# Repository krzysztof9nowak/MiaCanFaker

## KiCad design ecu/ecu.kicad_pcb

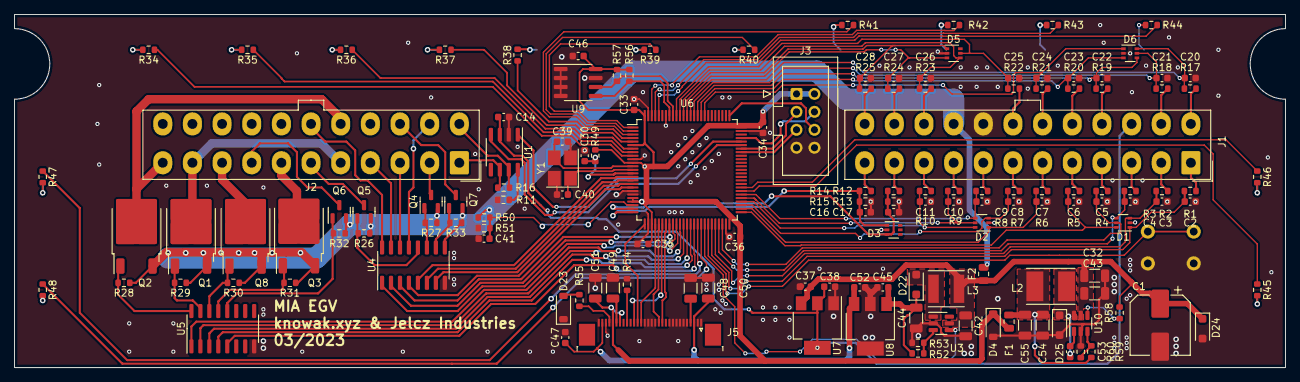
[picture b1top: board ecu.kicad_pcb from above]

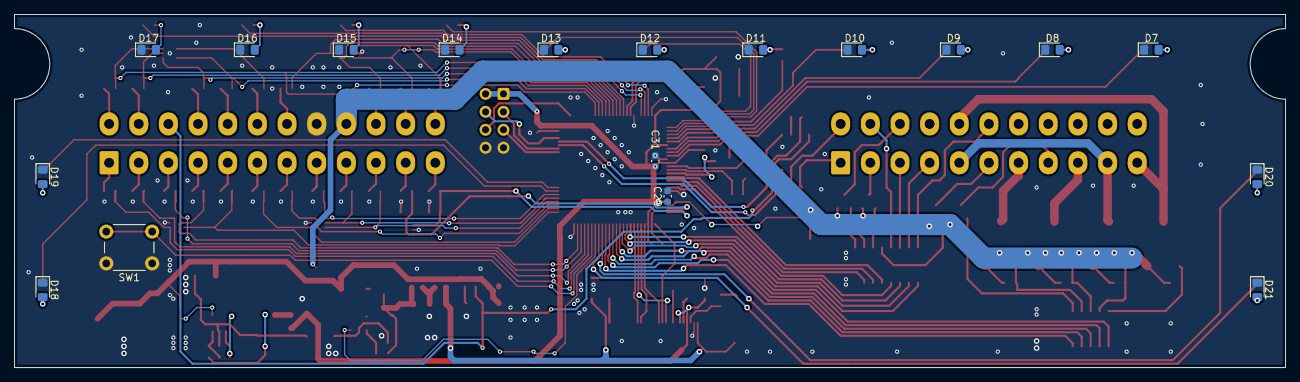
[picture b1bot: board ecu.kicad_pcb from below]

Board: 2 copper layers, 180.0 x 50.0 mm, 162 parts (18 on the bottom side), 145 nets.

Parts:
C1: 100uF 25V; CP_Elec_8x6.2
C2, C3, C4, C5, C6, C7, C8, C9, C10, C11, C14, C16, C17, C20, C21, C22, C23, C24, C25, C26, C27, C28, C41, C46: 100nF; C_0603_1608Metric
C29, C31, C33, C34, C35, C37, C38: 1uF; C_0603_1608Metric
C30, C53: 100n; C_0603_1608Metric
C32, C42, C43, C44, C48, C49, C50, C51: 10uF 25V; C_1206_3216Metric
C36: 4.7u; C_0603_1608Metric
C39, C40: 18pF; C_0603_1608Metric
C45, C47, C52: 0.1uF; C_0603_1608Metric
C54, C55: 22uF 10V; C_1206_3216Metric
D1, D2, D3, D5, D6: PESD3V3L5UY; SOT-363_SC-70-6
D4: BZT52C3V6; D_SOD-123
D7, D8, D9, D10, D11, D12, D13, D14, D15, D16, D17, D18, D19, D20, D21: RED; LED_0805_2012Metric_Pad1.15x1.40mm_HandSolder
D22, D24: SK12WA; D_SOD-123F
D23: 1N4148; D_SOD-123
D25: SK14WA; D_SOD-123F
F1, F2: 250mA; Fuse_0805_2012Metric
J1: INPUTS; Molex_Mini-Fit_Jr_5566-24A_2x12_P4.20mm_Vertical
J2: OUTPUTS; Molex_Mini-Fit_Jr_5566-22A_2x11_P4.20mm_Vertical
J3: DEBUG; IDC-Header_2x04_P2.54mm_Vertical
J5: OLED; TE_3-1734839-0_1x30-1MP_P0.5mm_Horizontal
L2: 22uH 900mA; L_Taiyo-Yuden_NR-50xx_HandSoldering
L3: 22uH; L_Taiyo-Yuden_NR-50xx
Q1, Q2, Q3, Q8: AOD4185; TO-252-2
Q4, Q5, Q6, Q7: BXT3800P06M; SOT-23
R1, R2, R3, R4, R5, R6, R7, R8, R9, R10, R12, R13, R14, R15, R17, R18, R19, R20, R21, R22, R23, R24, R25, R26, R27, R28, R29, R30, R31, R32, R33, R49, R51, R56, R57, R58, R59: 10k; R_0603_1608Metric
R11, R53: 1k; R_0603_1608Metric
R16: DNP; R_0603_1608Metric
R34, R35, R36, R37, R38, R39, R40, R41, R42, R43, R44, R45, R46, R47, R48: 220; R_0603_1608Metric
R50: 100k; R_0603_1608Metric
R52: 29k; R_0603_1608Metric
R54: 910k; R_0603_1608Metric
R55: 50; R_0603_1608Metric
R60: 3k; R_0603_1608Metric
SW1: DISP_BUTTON; SW_PUSH_6mm_H13mm
U1: MCP2551-I-SN; SOIC-8_3.9x4.9mm_P1.27mm
U3: SB6286; SOT-23-6
U4, U5: ULN2003; SOP-16_3.9x9.9mm_P1.27mm
U6: STM32F103VETx; LQFP-100_14x14mm_P0.5mm
U7: AMS1117-5.0; SOT-223-3_TabPin2
U8: 78L15MG-AA3-R; SOT-223-3_TabPin2
U9: FM24CL16B; SOIC-8_3.9x4.9mm_P1.27mm
U10: AOZ1282CI-1; SOT-23-6
Y1: 16MHz; Crystal_SMD_3225-4Pin_3.2x2.5mm_HandSoldering

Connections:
+3V3: C29.1, C31.1, C33.1, C34.1, C35.1, C36.1, C46.1, C51.1, D4.1 (K), F1.2, J3.1, J3.2, J5.24, J5.26, R49.1, R56.1, R57.1, U6.6 (VBAT), U6.11 (VDD), U6.21 (VREF+), U6.22 (VDDA), U6.28 (VDD), U6.50 (VDD), U6.75 (VDD), U6.100 (VDD), U9.8 (VDD)
+5V: C14.1, C38.1, J1.15, U1.3 (VDD), U7.2 (VO)
+12V: F2.2, J1.21, Q1.3 (S), Q2.3 (S), Q3.3 (S), Q4.2 (S), Q5.2 (S), Q6.2 (S), Q7.2 (S), Q8.3 (S), R26.1, R27.1, R28.1, R29.1, R30.1, R31.1, R32.1, R33.1, R50.1, U4.9 (COM)
+15V: C47.1, C50.1, C52.1, J5.3, J5.29, U8.3 (OUT)
/APC: U4.7 (I7), U6.17 (PC2)
/APC_H: J2.14, Q7.3 (D)
/BMS: U4.1 (I1), U6.35 (PB0)
/BMS_L: J2.17, U4.16 (O1)
/CAN1_RX: U1.4 (RXD), U6.70 (PA11)
/CAN1_TX: U1.1 (TXD), U6.71 (PA12)
/CAN_H: J2.12, R16.1, U1.7 (CANH)
/CAN_L: J2.1, R16.2, U1.6 (CANL)
/HEATING: U5.5 (I5), U6.40 (PE9)
/HEATING_H: J2.8, Q6.3 (D)
/INDIC_LEFT: U5.1 (I1), U6.36 (PB1)
/INDIC_LEFT_H: J2.11, J2.16, Q2.2 (D)
/INDIC_RIGHT: U5.2 (I2), U6.37 (PB2)
/INDIC_RIGHT_H: J2.5, J2.10, Q1.2 (D)
/INVERTER: U4.4 (I4), U6.18 (PC3)
/INVERTER_L: J2.13, U4.13 (O4)
/IN_AIRBAG: C20.1, D6.6 (K5), R17.1, U6.87 (PD6)
/IN_BRAKE_1: C10.1, D2.5 (K4), R9.1, U6.55 (PD8)
/IN_CEINT: C2.1, D1.1 (K1), R1.1, U6.45 (PE14)
/IN_CRASH: C28.1, D5.1 (K1), R25.1, U6.89 (PB3)
/IN_CTL_APC: C3.1, D1.3 (K2), R2.1, U6.46 (PE15)
/IN_DF_CONV: C22.1, D6.4 (K3), R19.1, U6.85 (PD4)
/IN_DISP: SW1.2 (B), U6.44 (PE13)
/IN_DRIVE_DIR_1: C6.1, D1.6 (K5), R5.1, U6.51 (PB12)
/IN_DRIVE_DIR_2: C23.1, D6.3 (K2), R20.1, U6.84 (PD3)
/IN_ECO: C4.1, D1.4 (K3), R3.1, U6.47 (PB10)
/IN_FOG_LIGHT: C8.1, D2.3 (K2), R7.1, U6.53 (PB14)
/IN_HIGHBEAM: C25.1, D5.5 (K4), R22.1, U6.91 (PB5)
/IN_INDICATOR_RIGHT: C9.1, D2.4 (K3), R8.1, U6.56 (PD9)
/IN_KEY1: C26.1, D5.4 (K3), R23.1, U6.90 (PB4)
/IN_KEY2: C27.1, D5.3 (K2), R24.1, U6.88 (PD7)
/IN_PARK: C21.1, D6.5 (K4), R18.1, U6.86 (PD5)
/IN_SIDELIGHTS: C11.1, D2.6 (K5), R10.1, U6.54 (PB15)
/IN_WINDSHIELD_HEAT: C5.1, D1.5 (K4), R4.1, U6.48 (PB11)
/IN_WINDSHIELD_JET: C24.1, D6.1 (K1), R21.1, U6.83 (PD2)
/IN_WIPER: C7.1, D2.1 (K1), R6.1, U6.52 (PB13)
/LED_ABS: R41.1, U6.3 (PE4)
/LED_AIRBAG: R40.1, U6.2 (PE3)
/LED_BATTERY: R42.1, U6.98 (PE1)
/LED_BATTERY_HV: R48.1, U6.42 (PE11)
/LED_BELT: R38.1, U6.4 (PE5)
/LED_BRAKE: R37.1, U6.5 (PE6)
/LED_CHARGING: R47.1, U6.41 (PE10)
/LED_ELECTR: R35.1, U6.8 (PC14)
/LED_FOG: R43.1, U6.97 (PE0)
/LED_HEADLIGHT: R46.1, U6.58 (PD11)
/LED_HEATER: R44.1, U6.96 (PB9)
/LED_INDICATOR: R39.1, U6.1 (PE2)
/LED_SIDELIGHTS: R45.1, U6.57 (PD10)
/LED_STOP: R36.1, U6.7 (PC13)
/LED_TEMP: R34.1, U6.9 (PC15)
/LIGHT_DAYTIME: U4.6 (I6), U6.16 (PC1)
/LIGHT_DAYTIME_H: J2.2, Q4.3 (D)
/LIGHT_HAZARD: U4.5 (I5), U6.15 (PC0)
/LIGHT_HAZARD_H: J2.6, Q5.3 (D)
/LIGHT_REVERSE: U5.4 (I4), U6.39 (PE8)
/LIGHT_REVERSE_H: J2.7, Q3.2 (D)
/LIGHT_STOP: U5.3 (I3), U6.38 (PE7)
/LIGHT_STOP_H: J2.9, Q8.2 (D)
/OLED_CS: J5.19, U6.26 (PA3)
/OLED_DC: J5.18, U6.29 (PA4)
/OLED_MOSI: J5.12, U6.32 (PA7)
/OLED_POWER_EN: U3.4 (EN), U6.43 (PE12)
/OLED_RES: J5.20, U6.31 (PA6)
/OLED_SCK: J5.13, U6.30 (PA5)
/SCL: R57.2, U6.92 (PB6), U9.6 (SCL)
/SDA: R56.2, U6.93 (PB7), U9.5 (SDA)
/SWDCLK: J3.6, U6.76 (PA14)
/SWDIO: J3.4, U6.72 (PA13)
/THR1: C17.2, D3.3 (K2), R12.1, R13.2, U6.24 (PA1)
/THR2: C16.2, D3.1 (K1), R14.1, R15.2, U6.25 (PA2)
/USART1_RX: J3.3, U6.69 (PA10)
/USART1_TX: J3.5, U6.68 (PA9)
/VBAT_MEAS: C41.1, R50.2, R51.1, U6.23 (PA0)
/WINDSHIELD_HEAT: U4.3 (I3), U6.33 (PC4)
/WINDSHIELD_HEAT_L: J2.3, U4.14 (O3)
/WIPERS: U4.2 (I2), U6.34 (PC5)
/WIPERS_L: J2.4, U4.15 (O2)
GND: C1.2, C2.2, C3.2, C4.2, C5.2, C6.2, C7.2, C8.2, C9.2, C10.2, C11.2, C14.2, C16.1, C17.1, C20.2, C21.2, C22.2, C23.2, C24.2, C25.2, C26.2, C27.2, C28.2, C29.2, C30.2, C31.2, C32.2, C33.2, C34.2, C35.2, C36.2, C37.2, C38.2, C39.2, C40.2, C41.2, C42.2, C43.2, C44.2, C45.2, C46.2, C47.2, C48.2, C49.2, C50.2, C51.2, C52.2, C54.2, C55.2, D1.2 (A), D2.2 (A), D3.2 (A), D4.2 (A), D5.2 (A), D6.2 (A), D7.1 (K), D8.1 (K), D9.1 (K), D10.1 (K), D11.1 (K), D12.1 (K), D13.1 (K), D14.1 (K), D15.1 (K), D16.1 (K), D17.1 (K), D18.1 (K), D19.1 (K), D20.1 (K), D21.1 (K), D23.1 (K), D24.2 (A), D25.2 (A), J1.20, J3.7, J3.8, J5.1, J5.2, J5.5, J5.6, J5.7, J5.8, J5.9, J5.10, J5.14, J5.15, J5.16, J5.17, J5.28, J5.30, R11.2, R13.1, R15.1, R51.2, R53.1, R54.1, R60.1, SW1.1 (A), U1.2 (VSS), U3.2 (GND), U4.8 (GND), U5.8 (GND), U6.10 (VSS), U6.19 (VSSA), U6.20 (VREF-), U6.27 (VSS), U6.49 (VSS), U6.74 (VSS), U6.94 (BOOT0), U6.99 (VSS), U7.1 (GND), U8.2 (GND), U9.1 (A0), U9.2 (A1), U9.3 (A2), U9.4 (VSS), U9.7 (WP), U10.2 (GND), Y1.2, Y1.4
unnamed: C54.1, C55.1, F1.1, L2.2, R59.2
unnamed: D7.2 (A), R34.2
unnamed: D8.2 (A), R35.2
unnamed: D9.2 (A), R36.2
unnamed: D10.2 (A), R37.2
unnamed: D11.2 (A), R38.2
unnamed: D12.2 (A), R39.2
unnamed: D13.2 (A), R40.2
unnamed: D14.2 (A), R41.2
unnamed: D15.2 (A), R42.2
unnamed: D16.2 (A), R43.2
unnamed: D17.2 (A), R44.2
unnamed: D18.2 (A), R45.2
unnamed: D19.2 (A), R46.2
unnamed: D20.2 (A), R47.2
unnamed: D21.2 (A), R48.2
unnamed: D22.2 (A), L3.2, U3.1 (SW)
unnamed: C44.1, C45.1, D22.1 (K), R52.2, U8.1 (IN)
unnamed: D23.2 (A), R55.1
unnamed: C1.1, C32.1, C37.1, C42.1, C43.1, D24.1 (K), F2.1, L3.1, R58.2, U3.5 (IN), U7.3 (VI), U10.5 (VIN)
unnamed: C53.1, D25.1 (K), L2.1, U10.6 (LX)
unnamed: J1.1, R1.2
unnamed: J1.2, R2.2
unnamed: J1.3, R3.2
unnamed: J1.4, R4.2
unnamed: J1.5, R5.2
unnamed: J1.6, R6.2
unnamed: J1.7, R7.2
unnamed: J1.8, R8.2
unnamed: J1.9, R9.2
unnamed: J1.10, R10.2
unnamed: J1.11, R12.2
unnamed: J1.12, R14.2
unnamed: J1.13, R17.2
unnamed: J1.14, R18.2
unnamed: J1.16, R19.2
unnamed: J1.17, R20.2
unnamed: J1.18, R21.2
unnamed: J1.19, R22.2
unnamed: J1.22, R23.2
unnamed: J1.23, R24.2
unnamed: J1.24, R25.2
unnamed: C48.1, J5.4
unnamed: J5.22, R54.2
unnamed: C49.1, J5.25
unnamed: J5.27, R55.2
unnamed: Q1.1 (G), R29.2, U5.15 (O2)
unnamed: Q2.1 (G), R28.2, U5.16 (O1)
unnamed: Q3.1 (G), R31.2, U5.13 (O4)
unnamed: Q4.1 (G), R27.2, U4.11 (O6)
unnamed: Q5.1 (G), R26.2, U4.12 (O5)
unnamed: Q6.1 (G), R32.2, U5.12 (O5)
unnamed: Q7.1 (G), R33.2, U4.10 (O7)
unnamed: Q8.1 (G), R30.2, U5.14 (O3)
unnamed: R11.1, U1.8 (Rs)
unnamed: R52.1, R53.2, U3.3 (FB)
unnamed: C30.1, R49.2, U6.14 (NRST)
unnamed: C39.1, U6.12 (OSC_IN), Y1.3
unnamed: C40.1, U6.13 (OSC_OUT), Y1.1
unnamed: C53.2, U10.1 (BST)
unnamed: R58.1, U10.4 (EN)
unnamed: R59.1, R60.2, U10.3 (FB)

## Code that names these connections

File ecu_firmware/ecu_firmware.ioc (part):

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Mcu.Name=STM32F103V(C-D-E)Tx
Mcu.Package=LQFP100
Mcu.UserName=STM32F103VETx
PA0-WKUP.GPIOParameters=GPIO_Label
PA0-WKUP.GPIO_Label=VBAT
PA0-WKUP.Signal=GPIO_Analog
PA1.GPIOParameters=GPIO_Label
PA1.GPIO_Label=THR1
PA1.Signal=SharedAnalog_PA1
PA10.Mode=Asynchronous
PA10.Signal=USART1_RX
PA11.Mode=CAN_Activate
PA11.Signal=CAN_RX
PA12.Mode=CAN_Activate
PA12.Signal=CAN_TX
PA13.Signal=SYS_JTMS-SWDIO
PA14.Signal=SYS_JTCK-SWCLK
PA2.GPIOParameters=GPIO_Label
PA2.GPIO_Label=THR2
PA2.Signal=SharedAnalog_PA2
PA3.GPIOParameters=GPIO_Label
PA3.GPIO_Label=OLED_CS
PA3.Signal=GPIO_Output
PA4.GPIOParameters=GPIO_Label
PA4.GPIO_Label=OLED_DC
PA4.Signal=GPIO_Output
PA5.Mode=TX_Only_Simplex_Unidirect_Master
PA5.Signal=SPI1_SCK
PA6.GPIOParameters=GPIO_Label
PA6.GPIO_Label=OLED_RES
PA6.Signal=GPIO_Output
PA7.Mode=TX_Only_Simplex_Unidirect_Master
PA7.Signal=SPI1_MOSI
PA9.Mode=Asynchronous
PA9.Signal=USART1_TX
PB0.GPIOParameters=GPIO_Label
PB0.GPIO_Label=BMS
PB0.Signal=GPIO_Output
PB1.GPIOParameters=GPIO_Label
PB1.GPIO_Label=INDIC_LEFT
PB1.Signal=GPIO_Output
PB10.GPIOParameters=GPIO_Label
PB10.GPIO_Label=IN_ECO
PB10.Signal=GPIO_Input
PB11.GPIOParameters=GPIO_Label
PB11.GPIO_Label=IN_WINDSHIELD_HEAT
PB11.Signal=GPIO_Input
PB12.GPIOParameters=GPIO_Label
PB12.GPIO_Label=IN_DRIVE_DIR_1
PB12.Signal=GPIO_Input
PB13.GPIOParameters=GPIO_Label
PB13.GPIO_Label=IN_WIPER
PB13.Signal=GPIO_Input
PB14.GPIOParameters=GPIO_Label
PB14.GPIO_Label=IN_FOG_LIGHT
PB14.Signal=GPIO_Input
PB15.GPIOParameters=GPIO_Label
PB15.GPIO_Label=IN_SIDELIGHT
PB15.Signal=GPIO_Input
PB2.GPIOParameters=GPIO_Label
PB2.GPIO_Label=INDIC_RIGHT
PB2.Signal=GPIO_Output
PB3.GPIOParameters=GPIO_Label
PB3.GPIO_Label=IN_CRASH
PB3.Signal=GPIO_Input
PB4.GPIOParameters=GPIO_Label
PB4.GPIO_Label=IN_KEY1
PB4.Signal=GPIO_Input
PB5.GPIOParameters=GPIO_Label
PB5.GPIO_Label=IN_HIGHBEAM
PB5.Signal=GPIO_Input
PB6.Mode=I2C
PB6.Signal=I2C1_SCL
PB7.Mode=I2C
PB7.Signal=I2C1_SDA
PB9.GPIOParameters=GPIO_Label
PB9.GPIO_Label=LED_HEATER
PB9.Signal=GPIO_Output
PC1.GPIOParameters=GPIO_Label
PC1.GPIO_Label=LIGHT_DAYTIME
PC1.Signal=GPIO_Output
PC13-TAMPER-RTC.GPIOParameters=GPIO_Label
PC13-TAMPER-RTC.GPIO_Label=LED_STOP
PC13-TAMPER-RTC.Signal=GPIO_Output
PC14-OSC32_IN.GPIOParameters=GPIO_Label
PC14-OSC32_IN.GPIO_Label=LED_ELECTR
PC14-OSC32_IN.Signal=GPIO_Output
PC15-OSC32_OUT.GPIOParameters=GPIO_Label
PC15-OSC32_OUT.GPIO_Label=LED_TEMP
PC15-OSC32_OUT.Signal=GPIO_Output
PC2.GPIOParameters=GPIO_Label
PC2.GPIO_Label=APC
PC2.Signal=GPIO_Output
PC3.GPIOParameters=GPIO_Label
PC3.GPIO_Label=INVERTER
PC3.Signal=GPIO_Output
PC4.GPIOParameters=GPIO_Label
PC4.GPIO_Label=WINDSHIELD_HEAT
PC4.Signal=GPIO_Output
PC5.GPIOParameters=GPIO_Label
PC5.GPIO_Label=WIPERS
PC5.Signal=GPIO_Output
PD10.GPIOParameters=GPIO_Label
PD10.GPIO_Label=LED_SIDELIGHTS
PD10.Signal=GPIO_Output
PD11.GPIOParameters=GPIO_Label
PD11.GPIO_Label=LED_HEADLIGHT
PD11.Signal=GPIO_Output
PD2.GPIOParameters=GPIO_Label
PD2.GPIO_Label=IN_WINDSHIELD_JET
PD2.Signal=GPIO_Input
PD3.GPIOParameters=GPIO_Label
PD3.GPIO_Label=IN_DRIVE_DIR_2
PD3.Signal=GPIO_Input
PD4.GPIOParameters=GPIO_Label
PD4.GPIO_Label=IN_DF_CONV
PD4.Signal=GPIO_Input
PD5.GPIOParameters=GPIO_PuPd,GPIO_Label
PD5.GPIO_Label=IN_PARK
PD5.GPIO_PuPd=GPIO_PULLUP
PD5.Signal=GPIO_Input
PD6.GPIOParameters=GPIO_Label
PD6.GPIO_Label=IN_AIRBAG
PD6.Signal=GPIO_Input
PD7.GPIOParameters=GPIO_Label
PD7.GPIO_Label=IN_KEY2
PD7.Signal=GPIO_Input
PD8.GPIOParameters=GPIO_Label
PD8.GPIO_Label=IN_BRAKE_1
PD8.Signal=GPIO_Input
PD9.GPIOParameters=GPIO_Label
PD9.GPIO_Label=IN_INDICATOR_RIGHT
PD9.Signal=GPIO_Input
PE0.GPIOParameters=GPIO_Label
PE0.GPIO_Label=LED_FOG
PE0.Signal=GPIO_Output
PE1.GPIOParameters=GPIO_Label
PE1.GPIO_Label=LED_BATTERY
PE1.Signal=GPIO_Output
PE10.GPIOParameters=GPIO_Label
PE10.GPIO_Label=LED_CHARGING
PE10.Signal=GPIO_Output
PE11.GPIOParameters=GPIO_Label
PE11.GPIO_Label=LED_BATTERY_HV
PE11.Signal=GPIO_Output
PE12.GPIOParameters=GPIO_Label
PE12.GPIO_Label=OLED_POWER_EN
PE12.Signal=GPIO_Output
PE13.GPIOParameters=GPIO_PuPd,GPIO_Label
PE13.GPIO_Label=IN_DISP
PE13.GPIO_PuPd=GPIO_PULLUP
PE13.Signal=GPXTI13
PE14.GPIOParameters=GPIO_Label
PE14.GPIO_Label=IN_CEINT
PE14.Signal=GPIO_Input
PE15.GPIOParameters=GPIO_Label
PE15.GPIO_Label=IN_CTL_APC
PE15.Signal=GPIO_Output
PE2.GPIOParameters=GPIO_Label
PE2.GPIO_Label=LED_INDICATOR
PE2.Signal=GPIO_Output
PE3.GPIOParameters=GPIO_Label
PE3.GPIO_Label=LED_AIRBAG
PE3.Signal=GPIO_Output
PE4.GPIOParameters=GPIO_Label
PE4.GPIO_Label=LED_ABS
PE4.Signal=GPIO_Output
PE5.GPIOParameters=GPIO_Label
PE5.GPIO_Label=LED_BELT
PE5.Signal=GPIO_Output
PE6.GPIOParameters=GPIO_Label
PE6.GPIO_Label=LED_BRAKE
PE6.Signal=GPIO_Output
PE7.GPIOParameters=GPIO_Label
PE7.GPIO_Label=LIGHT_STOP
PE7.Signal=GPIO_Output
PE8.GPIOParameters=GPIO_Label
PE8.GPIO_Label=LIGHT_REVERSE
PE8.Signal=GPIO_Output
PE9.GPIOParameters=GPIO_Label
PE9.GPIO_Label=HEATING
PE9.Signal=GPIO_Output
RCC.HSEDivPLL=RCC_HSE_PREDIV_DIV2
RCC.HSE_VALUE=16000000
RCC.SYSCLKFreq_VALUE=72000000
RCC.SYSCLKSource=RCC_SYSCLKSOURCE_PLLCLK
board=custom

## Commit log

2023-02-02 stop działał ale zmarł -a
2023-02-02 stop działał ale zmarł
2023-02-02 stop zadziałał:w
2023-02-02 fixed bms stop
2023-02-03 Add can_id, build list of all frames, improve display of frames
2023-02-03 Formatting, auto can_id when sending
2023-02-04 metaaaclasses
2023-02-04 send bms status after command
2023-02-04 charging
2023-02-04 diag attempts
2023-02-04 remove test file
2023-02-10 ignore bytes length mismatch
2023-02-10 Fake heartbeat
2023-02-10 filter fix
2023-02-10 change endian
2023-02-10 Disable heartbeat fake and uds, restore endian
2023-02-10 big endian
2023-02-10 fix meta
2023-02-10 fix2
2023-02-10 naprawiono stat 2 na pałę
2023-02-14 Michał pisze
2023-02-15 gitignore
2023-02-15 added DCF
2023-02-15 waveshare module to standard can lib
2023-02-15 comms with inverter
2023-02-15 playing with PDOs
2023-02-16 pdos
2023-02-16 kręcenie kołem
2023-02-18 fix bitfield of bms
2023-02-18 driving game
2023-02-19 print out messages
2023-03-10 ecu schematic
2023-03-15 stm dodany
2023-03-21 ecu schematic...
2023-03-31 pcb layout in progress
2023-04-02 pcb layout completed
2023-04-13 Blinken Lights with FreeRTOS
2023-04-13 remove build
2023-04-14 speedometer werks
2023-04-14 makefile autodetect c
2023-04-14 LED test
2023-04-14 CAN Cube configuration 500kbit/s
2023-04-14 ADC configuration
2023-04-14 Displaying ADC on the display
2023-04-14 Backup
2023-04-14 Got messed up
2023-04-14 Rabotajet
2023-04-14 Correct Mailboxes
2023-04-14 Done for today
2023-04-16 Tryin' interrupts
2023-04-22 Button interrupt
2023-04-23 can działa w polowaniu
2023-04-23 demo dla dyrektora
2023-05-01 charging works
2023-05-05 fixed
2023-05-05 Charging works full legit
2023-05-05 ładowarka perfect
2023-05-05 added mutex
2023-05-05 Changed coil PWM to 24V
2023-05-05 Motor temp controll quickfix
2023-05-06 saved cubemx
2023-05-06 ADC start kicked out and whatnot
2023-05-06 Works fine, but crashes
2023-05-06 Watchdog
2023-05-09 Fix crash in dashboard task
2023-05-09 Added smart stop
2023-05-10 Charging voltage
2023-05-16 Kalibracja
2023-05-16 Dodano kontrolki
2023-05-23 Changed controler temp type
2023-05-24 Bliinkers go fast
2023-05-30 Add gear indicator
2023-05-30 Add dummy submodule structure
2023-05-30 Add library target to the main project
2023-05-30 Implement drawing of simple graphics primitives
2023-05-30 Implement first version of analog speedo
2023-05-30 Finish implementing all main ui elements
2023-05-30 Implement efficient text drawing
2023-05-30 Improve performance of bitmap drawing
2023-05-30 Add popup framework + full ASCII font
2023-05-30 Add background to UI
2023-05-30 Update digit 3 in 4x7 font
2023-05-30 Initial suboptimal bitmap handling
2023-05-30 Implement triangle rasterizers
2023-05-30 Start developing actual UI
2023-05-30 Implement gfx preview frame for x86 using SDL2
2023-05-30 Add xor ops, tinting bitmaps
2023-05-30 Implement basic gfx functions
2023-05-30 Add static background bitmap support
2023-05-30 Update script to generate font resources
2023-05-30 Fix CMake configurations
2023-05-30 Implement antialiased lines using Wu's algorithm
2023-05-30 Fix arm build
2023-05-30 New display works
2023-05-30 Remove eco driving profile
2023-05-31 Remove u8g2 from project
2023-05-31 Try to setup CMake-based build
2023-06-01 CMake configuration finally works
2023-06-01 Setup CI build
2023-06-01 Fix arm inline assembly
2023-06-01 Add blinkers to dashboard
2023-06-01 Add speedometer averaging
2023-06-23 pacified CAN
2023-06-23 remove makefile
2023-06-23 magiczny tryb programowania sevcon
2023-06-23 increase charging voltage 92V
2023-06-25 change cell count on dashboard
2023-06-25 Added DCF config file for Sevcon, with modified voltage
2023-09-24 Attempt at hazard lights
2023-09-24 Podłączenie świateł stopu do pedału hamulca
2023-09-25 Światła stopu
2023-09-25 battery graph
2023-10-20 Latest fixes
2023-10-21 Added Neutral Gear
2023-10-27 commands changed
2025-02-24 bckp
